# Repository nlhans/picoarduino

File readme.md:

## (yet another) pico at arduino form factor board thingy

Wishlist: 
- power socket with 5V regulator (Vsys) also linked to Vin (shield compatibility)
- jumper switches (solder bridges on PCB bottom) for power selection: 5V or 3.3V
- multiplexer for 6 analog inputs (74HC4053?)

comments on first edition: 

Aangepaste schema/PCB layout voor een Raspberry Pico in Arduino jasje.

Uno compatible pinnen voor de Pico is niet gestandaardiseerd. Dus pinning overgenomen van FlexyPin versie: https://shop.pimoroni.com/products/raspberry-pi-pico-to-uno-flexypin-adapter?variant=40387747414099

A4-A6 zijn toegevoegd middels 74HC4053 mux en geschakeld met GPIO22. Hierdoor ontbreekt SCL/SDA helaas wel op A5/A6.

Verdere poorten:
SPI0 is op D10-D13 (losse 6-pin).
SPI1 zit op D16-D19.
I2C0 zit op D20/D21.
I2C1 zit o.a. op D2/D3.
UART0 zit op D0/D1.

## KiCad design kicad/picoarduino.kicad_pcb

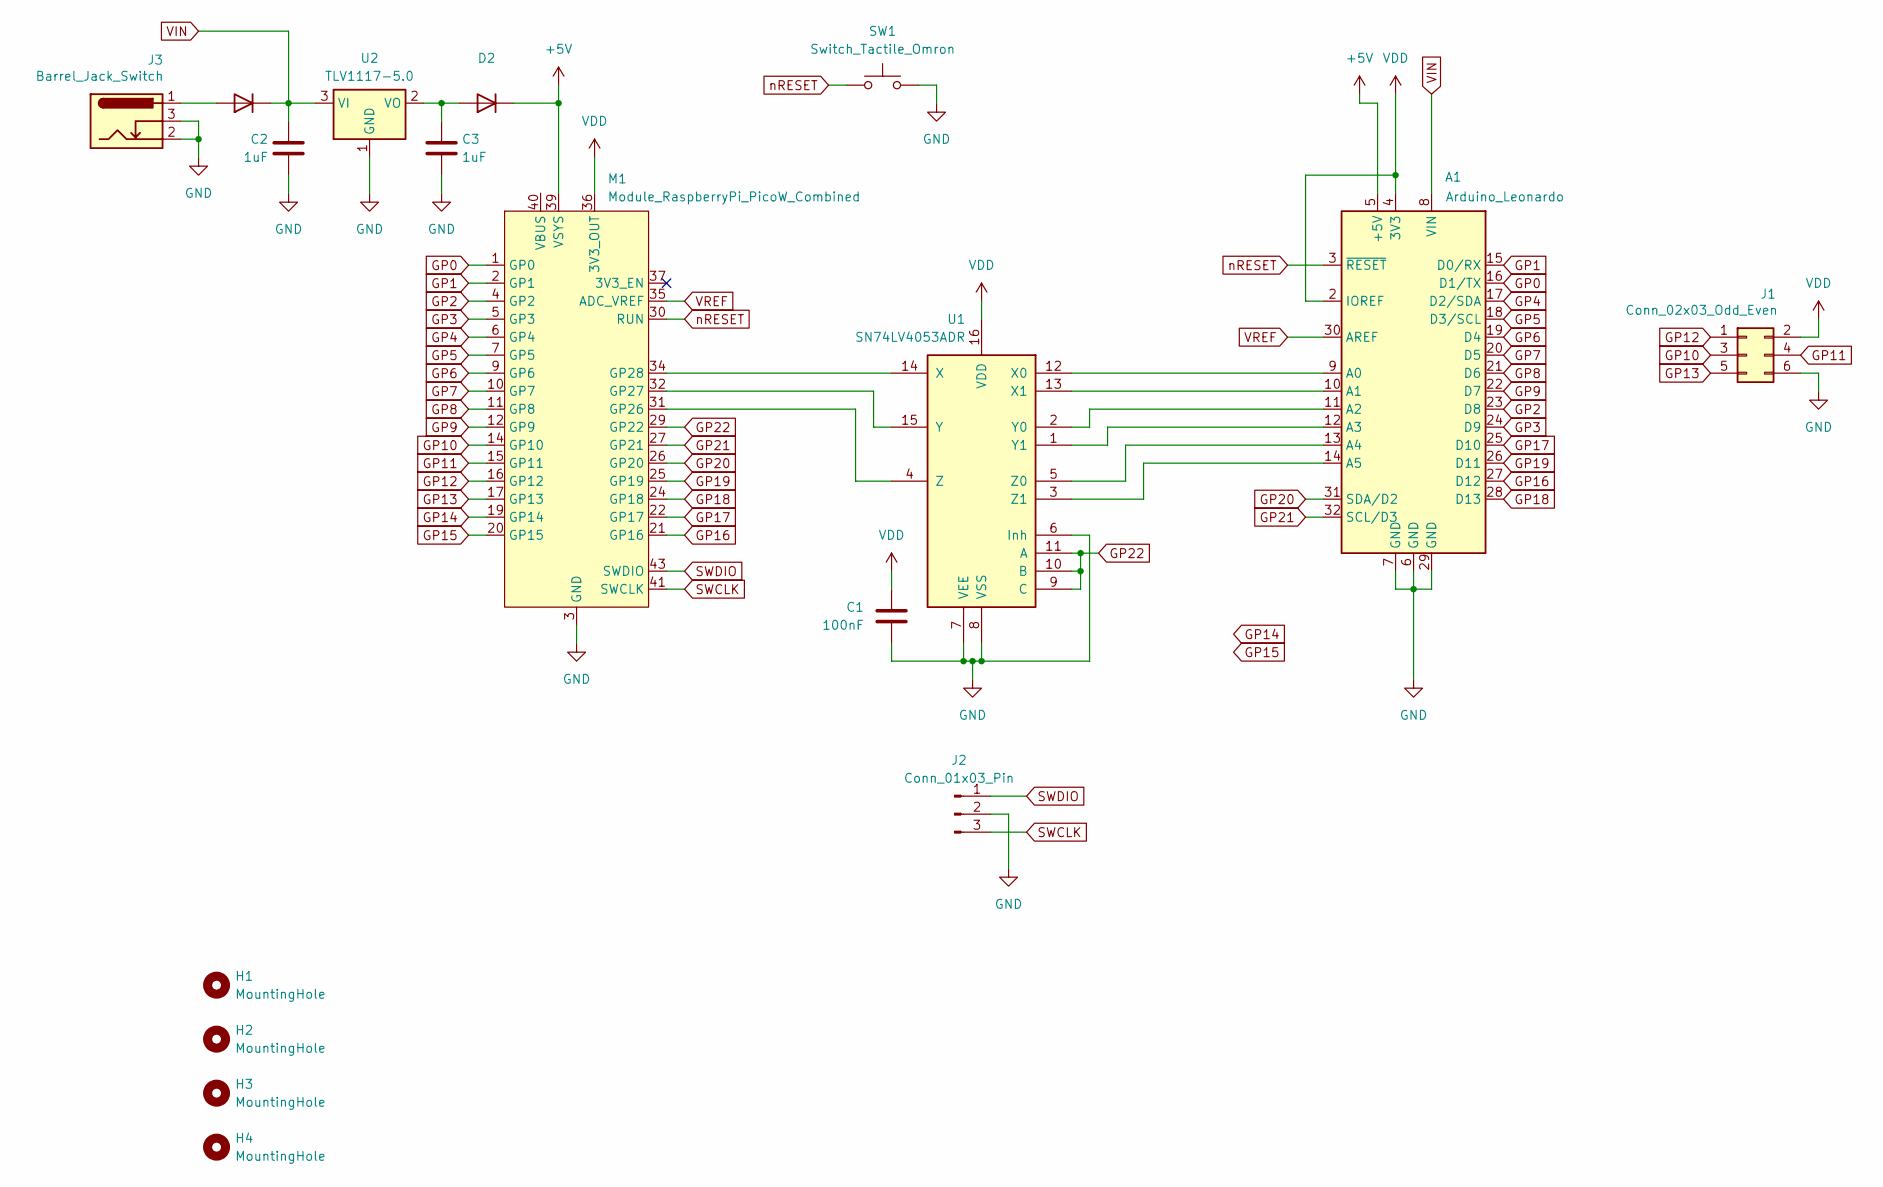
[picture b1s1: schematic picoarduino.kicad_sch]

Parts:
A1: Arduino_Leonardo; Arduino_UNO_R3
C1: 100nF; C_1206_3216Metric_Pad1.33x1.80mm_HandSolder
C2, C3: 1uF; C_1206_3216Metric_Pad1.33x1.80mm_HandSolder
D1, D2: D_SMB
H1, H2, H3, H4: MountingHole; MountingHole_3.2mm_M3_DIN965
J1: Conn_02x03_Odd_Even; PinHeader_2x03_P2.54mm_Vertical
J2: Conn_01x03_Pin; PinHeader_1x03_P2.54mm_Horizontal
J3: Barrel_Jack_Switch; BarrelJack_Horizontal
M1: Module_RaspberryPi_PicoW_Combined; RaspberryPi_Pico
SW1: Switch_Tactile_Omron; Button_Omron_B3SN_6.0x6.0mm
U1: SN74LV4053ADR; SOIC-16_3.9x9.9mm_P1.27mm; MPN SN74LV4053ADR
U2: TLV1117-5.0; SOT-223-3_TabPin2

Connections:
+5V: A1.5 (+5V), D2.1 (K), M1.39 (VSYS)
GND: A1.6 (GND), A1.7 (GND), A1.29 (GND), C1.2, C2.2, C3.2, J1.6, J2.2, J3.2, J3.3, M1.3 (GND), M1.8 (GND), M1.13 (GND), M1.18 (GND), M1.23 (GND), M1.28 (GND), M1.33 (GND), M1.38 (GND), M1.42 (GND), SW1.2, U1.6 (Inh), U1.7 (VEE), U1.8 (VSS), U2.1 (GND)
GP0: A1.16 (D1/TX), M1.1 (GP0)
GP1: A1.15 (D0/RX), M1.2 (GP1)
GP2: A1.23 (D8), M1.4 (GP2)
GP3: A1.24 (D9), M1.5 (GP3)
GP4: A1.17 (D2/SDA), M1.6 (GP4)
GP5: A1.18 (D3/SCL), M1.7 (GP5)
GP6: A1.19 (D4), M1.9 (GP6)
GP7: A1.20 (D5), M1.10 (GP7)
GP8: A1.21 (D6), M1.11 (GP8)
GP9: A1.22 (D7), M1.12 (GP9)
GP10: J1.3, M1.14 (GP10)
GP11: J1.4, M1.15 (GP11)
GP12: J1.1, M1.16 (GP12)
GP13: J1.5, M1.17 (GP13)
GP14: M1.19 (GP14)
GP15: M1.20 (GP15)
GP16: A1.27 (D12), M1.21 (GP16)
GP17: A1.25 (D10), M1.22 (GP17)
GP18: A1.28 (D13), M1.24 (GP18)
GP19: A1.26 (D11), M1.25 (GP19)
GP20: A1.31 (SDA/D2), M1.26 (GP20)
GP21: A1.32 (SCL/D3), M1.27 (GP21)
GP22: M1.29 (GP22), U1.9 (C), U1.10 (B), U1.11 (A)
unnamed: A1.9 (A0), U1.12 (X0)
unnamed: A1.10 (A1), U1.13 (X1)
unnamed: A1.11 (A2), U1.2 (Y0)
unnamed: A1.12 (A3), U1.1 (Y1)
unnamed: A1.13 (A4), U1.5 (Z0)
unnamed: A1.14 (A5), U1.3 (Z1)
unnamed: D1.2 (A), J3.1
unnamed: C3.1, D2.2 (A), U2.2 (VO)
unnamed: M1.31 (GP26), U1.4 (Z)
unnamed: M1.32 (GP27), U1.15 (Y)
unnamed: M1.34 (GP28), U1.14 (X)
SWCLK: J2.3, M1.41 (SWCLK)
SWDIO: J2.1, M1.43 (SWDIO)
VDD: A1.2 (IOREF), A1.4 (3V3), C1.1, J1.2, M1.36 (3V3_OUT), U1.16 (VDD)
VIN: A1.8 (VIN), C2.1, D1.1 (K), U2.3 (VI)
VREF: A1.30 (AREF), M1.35 (ADC_VREF)
nRESET: A1.3 (~RESET), M1.30 (RUN), SW1.1

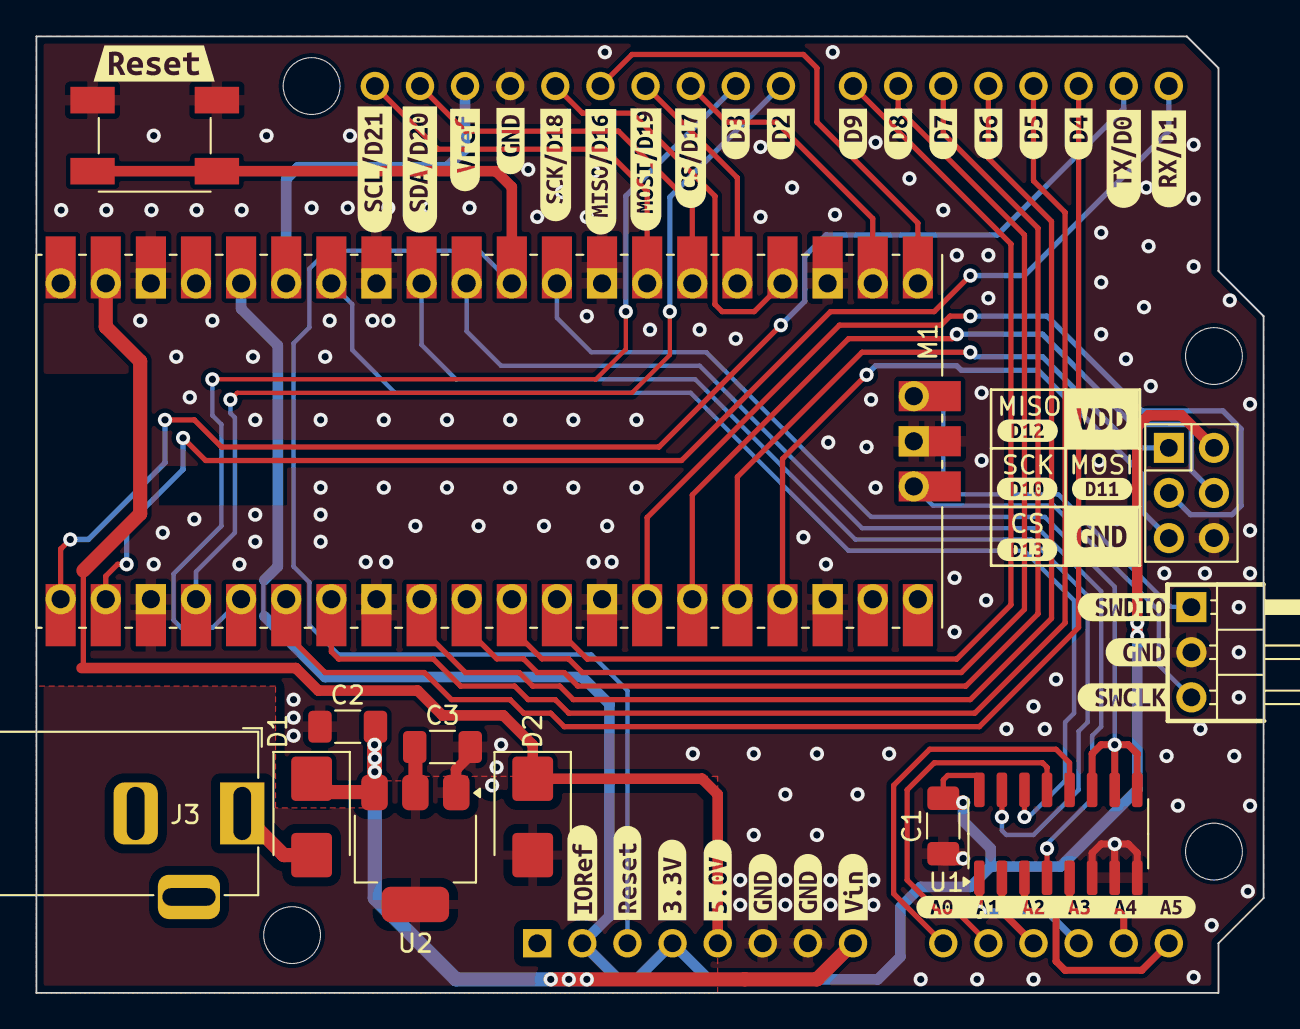
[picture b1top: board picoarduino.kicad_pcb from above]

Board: 2 copper layers, 69.1 x 53.8 mm, 53 parts (1 on the bottom side), 40 nets.

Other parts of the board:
kibuzzard-6811E7BB: G***; kibuzzard-6811E7BB
kibuzzard-6811E7CA: G***; kibuzzard-6811E7CA
kibuzzard-6811E7F6: G***; kibuzzard-6811E7F6
kibuzzard-6811E7FD: G***; kibuzzard-6811E7FD
kibuzzard-6811E8A2: G***; kibuzzard-6811E8A2
kibuzzard-6811E8AA: G***; kibuzzard-6811E8AA
kibuzzard-6811E8B1: G***; kibuzzard-6811E8B1
kibuzzard-6811E8BA: G***; kibuzzard-6811E8BA
kibuzzard-6811E8E7: G***; kibuzzard-6811E8E7
kibuzzard-6811E8EF: G***; kibuzzard-6811E8EF
kibuzzard-6811E80A: G***; kibuzzard-6811E80A
kibuzzard-6811E81B: G***; kibuzzard-6811E81B
kibuzzard-6811E84F: G***; kibuzzard-6811E84F
kibuzzard-6811E88B: G***; kibuzzard-6811E88B
kibuzzard-6811E89B: G***; kibuzzard-6811E89B
kibuzzard-6811E805: G***; kibuzzard-6811E805
kibuzzard-6811E813: G***; kibuzzard-6811E813
kibuzzard-6811E822: G***; kibuzzard-6811E822
kibuzzard-6811E893: G***; kibuzzard-6811E893
kibuzzard-6811E907: G***; kibuzzard-6811E907
kibuzzard-6811ECD5: G***; kibuzzard-6811ECD5
kibuzzard-6811ECDC: G***; kibuzzard-6811ECDC
kibuzzard-6811ED2E: G***; kibuzzard-6811ED2E
kibuzzard-6811ED4D: G***; kibuzzard-6811ED4D
kibuzzard-6811ED38: G***; kibuzzard-6811ED38
kibuzzard-6811ED44: G***; kibuzzard-6811ED44
kibuzzard-6811ED69: G***; kibuzzard-6811ED69
kibuzzard-6811ED70: G***; kibuzzard-6811ED70
kibuzzard-6811EEF0: G***; kibuzzard-6811EEF0
kibuzzard-681112EB: G***; kibuzzard-681112EB
kibuzzard-681112F5: G***; kibuzzard-681112F5
kibuzzard-681112FC: G***; kibuzzard-681112FC
kibuzzard-681135A2: G***; kibuzzard-681135A2
kibuzzard-68111259: G***; kibuzzard-68111259
kibuzzard-68111301: G***; kibuzzard-68111301
kibuzzard-68113590: G***; kibuzzard-68113590

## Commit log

2025-04-09 Create readme.md
    added readme
2025-04-09 added kicad files and datasheets
2025-04-30 Schematic and PCB
2025-07-18 Bill of materials
